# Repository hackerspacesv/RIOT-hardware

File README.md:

Hackerspace San Salvador RIOT OS Development Boards
===================================================
This repository contains all the design files for the boards supported by the
[RIOT OS](https://www.riot-os.org/) port mantained by the [Hackerspace
San Salvador](http://hackerspace.teubi.co/). You can find the RIOT OS port 
for the supported boards over
[https://github.com/hackerspacesv/RIOT](https://github.com/hackerspacesv/RIOT).

### Current boards supported
* **[ATSAMR21 Breakout Board](http://hackerspace.teubi.co/wiki/index.php?title=HSSV_ATSAMR21_Breakout_English)**: A development board to accelerate the deployment of
  IEEE 802.15.4 based networks on the 2.4Ghz band. It is based on the
  ATSAMR21G18-MR210UA module wich also includes support for antenna-diversity and
  a crypto-acceleration chip. This board was designed to be breadboard-friendly
  and includes USB support and power & LiPo battery management.
* **ATZB-RF-233-1-C breakout**: This is a breadboard-friendly breakout board for the
  module ATZB-RF-233-1-C, this module includes the easy-to-use AT8RF233 radio with
  a front-end-module with a Power-Amplifier & Low-Noise-Amplifier (PA/LNA) to greatly
  extend the range of the radio of IEEE 802.15.4 networks on the 2.4GHz band.

### Planned support
* **ATZB-RF-233-1-C breakout for the Omega Onion**: The Omega Onion is a low-cost
  system-on-a-module that runs a lightweight version of GNU/Linux. This breakout board
  should facilitate the creation of low-cost WiFi-802.15.4 bridges and edge routers.

### Board documentation

A guide to use this board with RIOT OS is available at the [Hackerspace San Salvador Wiki](http://hackerspace.teubi.co/wiki/index.php?title=HSSV_ATSAMR21_Breakout_English)

### Licensing and use
**Copyright 2018 Mario Gomez <mario.gomez@teubi.co>**

All files within this repository are licensed under the
Apache License, Version 2.0 (the "License") unless otherwise
specified in the individual files; you may not use this files
except in compliance with the License.

You may obtain a copy of the License at

    http://www.apache.org/licenses/LICENSE-2.0

Unless required by applicable law or agreed to in writing, software
and design files distributed under the License are distributed on an
"AS IS" BASIS, WITHOUT WARRANTIES OR CONDITIONS OF ANY KIND, either
express or implied.

See the License for the specific language governing permissions and
limitations under the License.

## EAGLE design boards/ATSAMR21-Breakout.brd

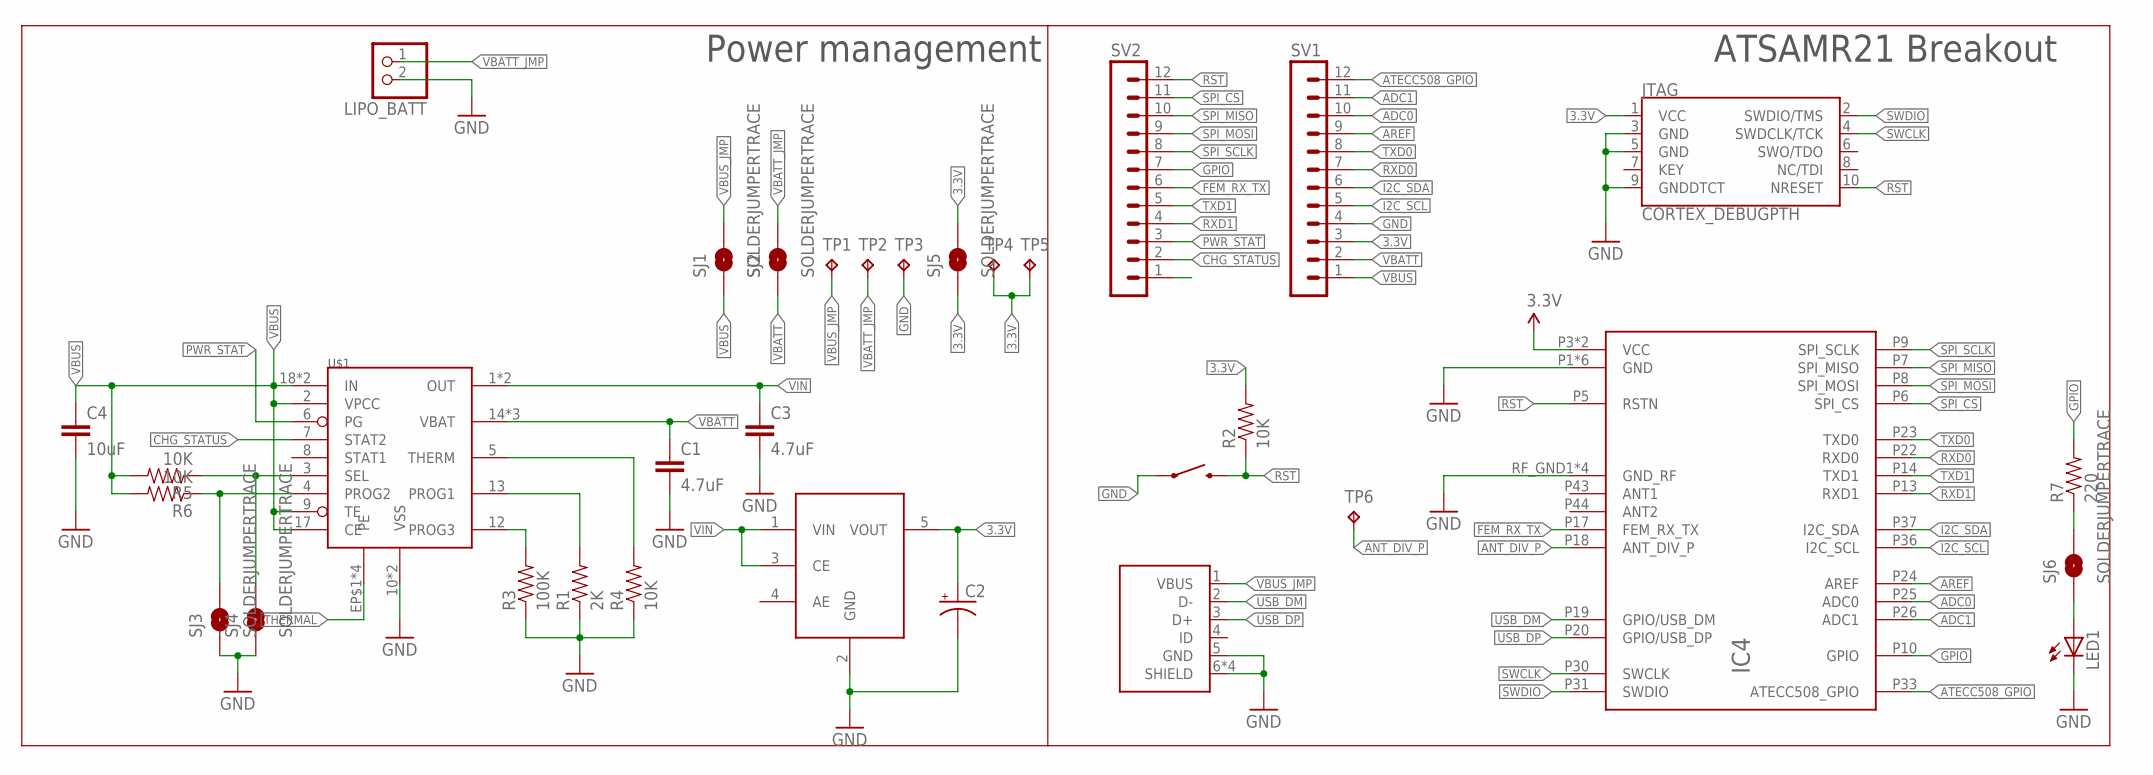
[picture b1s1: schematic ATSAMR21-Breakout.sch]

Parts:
C1, C3: 4.7uF; 0805
C2: 47uF; 1210-POLARIZED
C4: 10uF; 0805
IC3: NCP4589DSN33T1G; SOT23-5
IC4: ATSAMR21G18-MR210UA; ATSAMR21G18A-MR210UA
JTAG: CORTEX_DEBUGPTH; 2X5-PTH-1.27MM
LED1: LEDCHIPLED_1206; CHIPLED_1206
LIPO_BATT: JST_2PIN-THM-RA; JST-PH-2-THM-RA
R1: 2K; 0805
R2, R4, R5, R6: 10K; 0805
R3: 100K; 0805
R7: 220; 0805
S1: EVQ-PNF04M; PANASONIC_EVQPE1/PN/5P
SJ1, SJ2, SJ3, SJ4, SJ5, SJ6: SOLDERJUMPERTRACE; SJ_2S-TRACE
SV1, SV2: MA12-1
TP1, TP2, TP3, TP4, TP5, TP6: TPTP15R; TP15R
U$1: MCP73871T; QFN-20
USB_CONN: USB-MICRO-B; HPL511

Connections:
3.3V: C2.1 (+), IC3.5 (VOUT), IC4.P3 (VCC), IC4.P4 (VCC), JTAG.1 (VCC), R2.2, SJ5.1, SJ5.2, SV1.3, TP4.TP, TP5.TP
ADC0: IC4.P25 (ADC0), SV1.10
ADC1: IC4.P26 (ADC1), SV1.11
ANT_DIV_P: IC4.P18 (ANT_DIV_P), TP6.TP
AREF: IC4.P24 (AREF), SV1.9
ATECC508_GPIO: IC4.P33 (ATECC508_GPIO), SV1.12
CHG_STATUS: SV2.2, U$1.7 (STAT2)
FEM_RX_TX: IC4.P17 (FEM_RX_TX), SV2.6
GND: C1.2, C2.2 (-), C3.2, C4.2, IC3.2 (GND), IC4.P1 (GND), IC4.P2 (GND), IC4.P12 (GND), IC4.P29 (GND), IC4.P41 (GND), IC4.P42 (GND), IC4.RF_GND1 (GND_RF), IC4.RF_GND2 (GND_RF), IC4.RF_GND3 (GND_RF), IC4.RF_GND4 (GND_RF), JTAG.3 (GND), JTAG.5 (GND), JTAG.9 (GNDDTCT), LED1.C, LIPO_BATT.2 (1), R1.1, R3.1, R4.1, S1.P1 (1), SJ3.1, SJ4.1, SV1.4, SV2.1, TP3.TP, U$1.10 (VSS), U$1.11 (VSS), USB_CONN.5 (GND), USB_CONN.6 (SHIELD), USB_CONN.7 (SHIELD), USB_CONN.8 (SHIELD), USB_CONN.9 (SHIELD)
GPIO: IC4.P10 (GPIO), R7.2, SV2.7
I2C_SCL: IC4.P36 (I2C_SCL), SV1.5
I2C_SDA: IC4.P37 (I2C_SDA), SV1.6
unnamed: R6.1, SJ3.2, U$1.4 (PROG2)
unnamed: R5.1, SJ4.2, U$1.3 (SEL)
unnamed: R3.2, U$1.12 (PROG3)
unnamed: R1.2, U$1.13 (PROG1)
unnamed: R4.2, U$1.5 (THERM)
unnamed: LED1.A, SJ6.1
unnamed: R7.1, SJ6.2
PWR_STAT: SV2.3, U$1.6 (PG)
RST: IC4.P5 (RSTN), JTAG.10 (NRESET), R2.1, S1.P2 (2), SV2.12
RXD0: IC4.P22 (RXD0), SV1.7
RXD1: IC4.P13 (RXD1), SV2.4
SPI_CS: IC4.P6 (SPI_CS), SV2.11
SPI_MISO: IC4.P7 (SPI_MISO), SV2.10
SPI_MOSI: IC4.P8 (SPI_MOSI), SV2.9
SPI_SCLK: IC4.P9 (SPI_SCLK), SV2.8
SWCLK: IC4.P30 (SWCLK), JTAG.4 (SWDCLK/TCK)
SWDIO: IC4.P31 (SWDIO), JTAG.2 (SWDIO/TMS)
THERMAL: U$1.EP$1 (PE), U$1.EP$2 (PE), U$1.EP$3 (PE), U$1.EP$4 (PE)
TXD0: IC4.P23 (TXD0), SV1.8
TXD1: IC4.P14 (TXD1), SV2.5
USB_DM: IC4.P19 (GPIO/USB_DM), USB_CONN.2 (D-)
USB_DP: IC4.P20 (GPIO/USB_DP), USB_CONN.3 (D+)
VBATT: C1.1, SJ2.1, SV1.2, U$1.14 (VBAT), U$1.15 (VBAT), U$1.16 (VBAT)
VBATT_JMP: LIPO_BATT.1 (2), SJ2.2, TP2.TP
VBUS: C4.1, R5.2, R6.2, SJ1.1, SV1.1, U$1.2 (VPCC), U$1.9 (TE), U$1.17 (CE), U$1.18 (IN), U$1.19 (IN)
VBUS_JMP: SJ1.2, TP1.TP, USB_CONN.1 (VBUS)
VIN: C3.1, IC3.1 (VIN), IC3.3 (CE), U$1.1 (OUT), U$1.20 (OUT)

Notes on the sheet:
Power management
ATSAMR21 Breakout

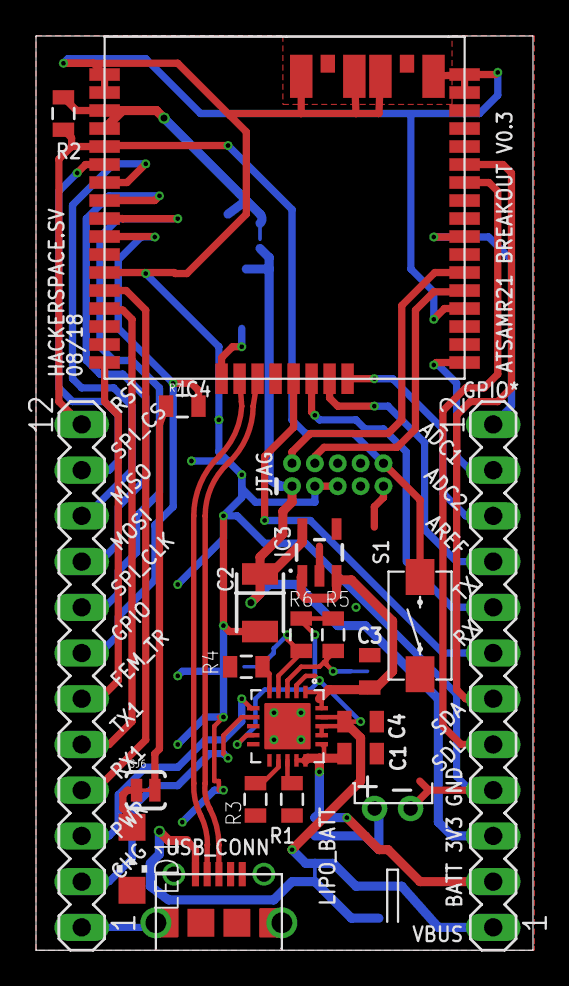
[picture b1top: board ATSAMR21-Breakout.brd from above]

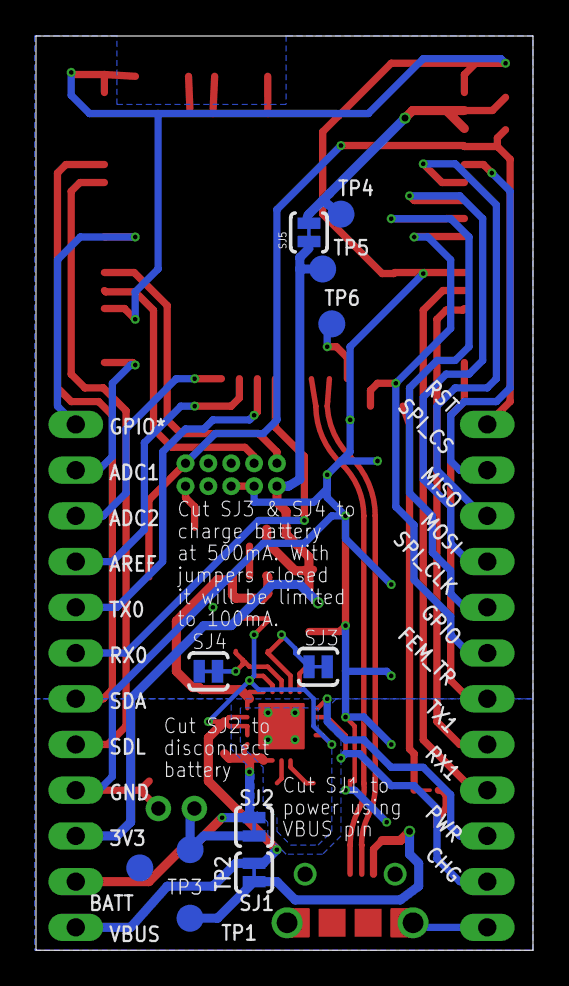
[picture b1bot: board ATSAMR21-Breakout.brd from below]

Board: 2 copper layers, 27.6 x 50.8 mm, 33 parts (11 on the bottom side), 39 nets.

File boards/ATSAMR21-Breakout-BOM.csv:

"Qty";"Value";"Device";"Package";"Parts";"Description";"MF";"MPN";"OC_FARNELL";"OC_NEWARK";"PROD_ID";"TP_SIGNAL_NAME";"VALUE";
"1";"";"JST_2PIN-THM-RA";"JST-PH-2-THM-RA";"LIPO_BATT";"JST 2-Pin Connectors of various flavors";"";"";"";"";"";"";"";
"2";"";"MA12-1";"MA12-1";"SV1, SV2";"PIN HEADER";"";"";"unknown";"unknown";"";"";"";
"1";"100K";"RESISTOR0805-RES";"0805";"R3";"Resistor";"";"";"";"";"";"";"";
"4";"10K";"RESISTOR0805-RES";"0805";"R2, R4, R5, R6";"Resistor";"";"";"";"";"";"";"";
"1";"10uF";"22UF-0805-6.3V-20%";"0805";"C4";"22µF ceramic capacitors";"";"";"";"";"CAP-08402";"";"22uF";
"1";"2K";"RESISTOR0805-RES";"0805";"R1";"Resistor";"";"";"";"";"";"";"";
"2";"4.7uF";"22UF-0805-6.3V-20%";"0805";"C1, C3";"22µF ceramic capacitors";"";"";"";"";"CAP-08402";"";"22uF";
"1";"47uF";"TPSB107M010R0400";"1210-POLARIZED";"C2";"";"";"";"";"";"";"";"";
"1";"ATSAMR21G18-MR210UA";"ATSAMR21G18-MR210UA";"ATSAMR21G18A-MR210UA";"IC4";"";"";"";"";"";"";"";"";
"1";"CORTEX_DEBUGPTH";"CORTEX_DEBUGPTH";"2X5-PTH-1.27MM";"JTAG";"Cortex Debug Connector";"";"";"";"";"";"";"";
"1";"EVQ-PNF04M";"EVQ-PNF04M";"PANASONIC_EVQPE1/PN/5P";"S1";"";"";"";"";"";"";"";"";
"1";"MCP73871T";"MCP73871T";"QFN-20";"U$1";"";"";"";"";"";"";"";"";
"1";"NCP4589DSN33T1G";"NCP4589DSN33T1G";"SOT23-5";"IC3";"";"";"";"";"";"";"";"";
"4";"SOLDERJUMPERTRACE";"SOLDERJUMPERTRACE";"SJ_2S-TRACE";"SJ1, SJ2, SJ3, SJ4";"Solder Jumper";"";"";"";"";"";"";"";
"3";"TPB2,54";"TPB2,54";"B2,54";"TP1, TP2, TP3";"Test pad";"";"";"";"";"";"";"";
"1";"USB-MICRO-B";"USB-MICRO-B";"HPL511";"USB_CONN";"";"";"";"";"";"";"";"";

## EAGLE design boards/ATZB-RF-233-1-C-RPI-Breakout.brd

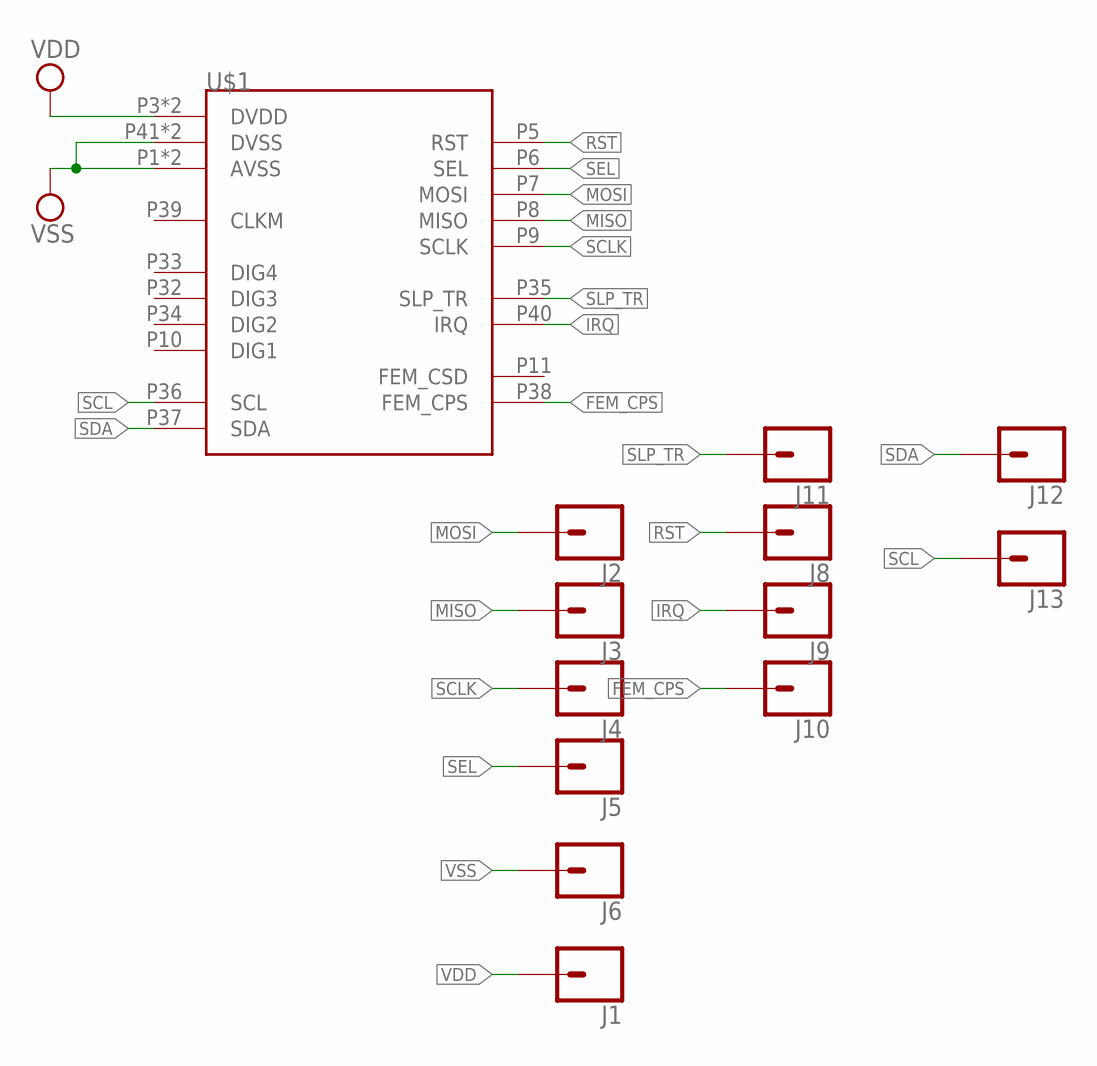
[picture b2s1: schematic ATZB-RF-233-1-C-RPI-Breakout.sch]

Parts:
J1, J2, J3, J4, J5, J6, J8, J9, J10, J11, J12, J13: CONN_01OFFSET; 1X01_OFFSET
U$1: ATZB-RF-233-1-C

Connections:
FEM_CPS: J10.1, U$1.P38 (FEM_CPS)
IRQ: J9.1, U$1.P40 (IRQ)
MISO: J3.1, U$1.P8 (MISO)
MOSI: J2.1, U$1.P7 (MOSI)
RST: J8.1, U$1.P5 (RST)
SCL: J13.1, U$1.P36 (SCL)
SCLK: J4.1, U$1.P9 (SCLK)
SDA: J12.1, U$1.P37 (SDA)
SEL: J5.1, U$1.P6 (SEL)
SLP_TR: J11.1, U$1.P35 (SLP_TR)
VDD: J1.1, U$1.P3 (DVDD), U$1.P4 (DVDD)
VSS: J6.1, U$1.P1 (AVSS), U$1.P2 (AVSS), U$1.P41 (DVSS), U$1.P42 (DVSS)

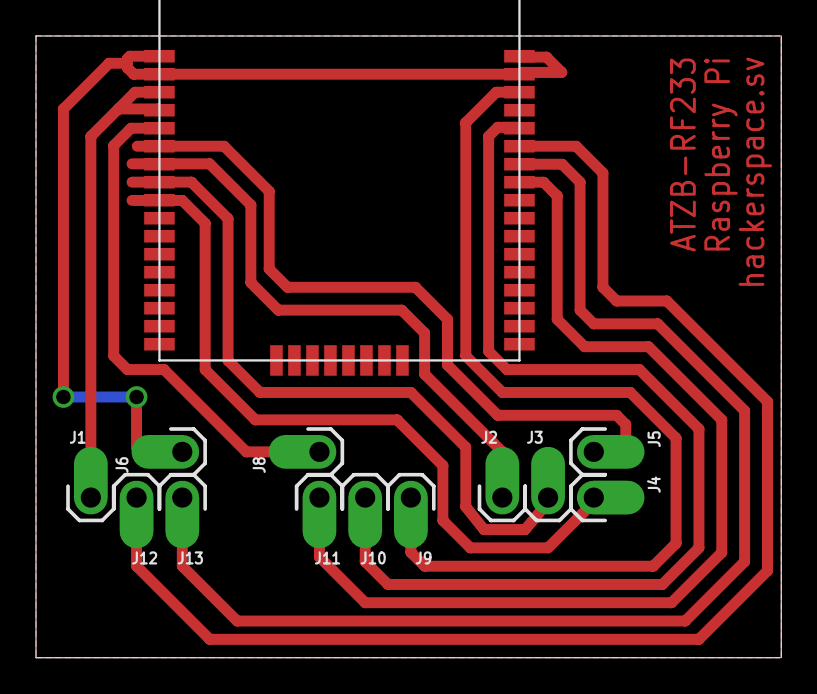
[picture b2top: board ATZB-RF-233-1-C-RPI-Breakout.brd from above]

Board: 2 copper layers, 41.4 x 34.5 mm, 13 parts (0 on the bottom side), 12 nets.

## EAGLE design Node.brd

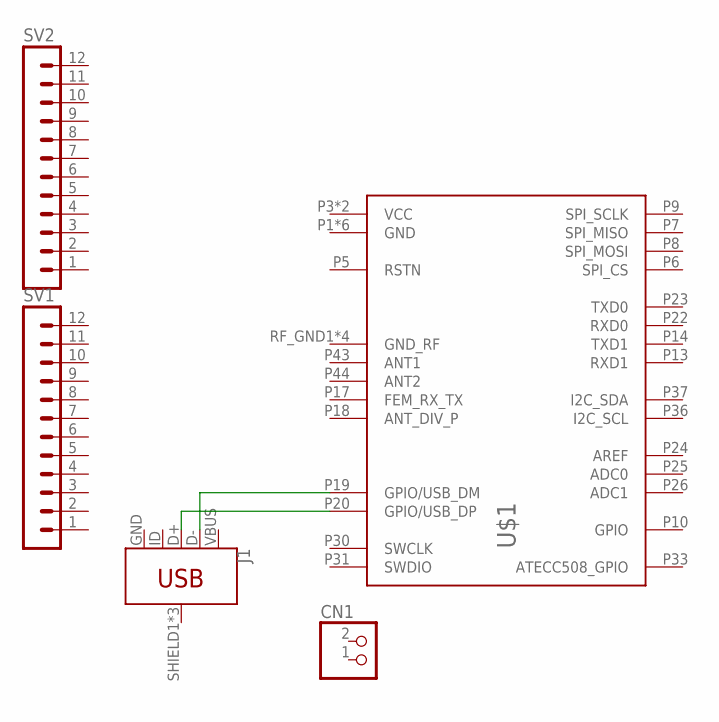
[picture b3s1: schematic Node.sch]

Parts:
CN1: JST_2PIN-THM-RA; JST-PH-2-THM-RA
J1: USB_MICRO-B_FEMALE-SMT; USB-B-MICRO-SMD
SV1, SV2: MA12-1
U$1: ATSAMR21G18-MR210UA; ATSAMR21G18A-MR210UA

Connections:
AREF: U$1.P24 (AREF)
GND: J1.GND, U$1.P1 (GND), U$1.P2 (GND), U$1.P12 (GND), U$1.P29 (GND), U$1.P41 (GND), U$1.P42 (GND)
unnamed: J1.D-, U$1.P19 (GPIO/USB_DM)
unnamed: J1.D+, U$1.P20 (GPIO/USB_DP)
VBUS: J1.VBUS
VCC: U$1.P3 (VCC), U$1.P4 (VCC)

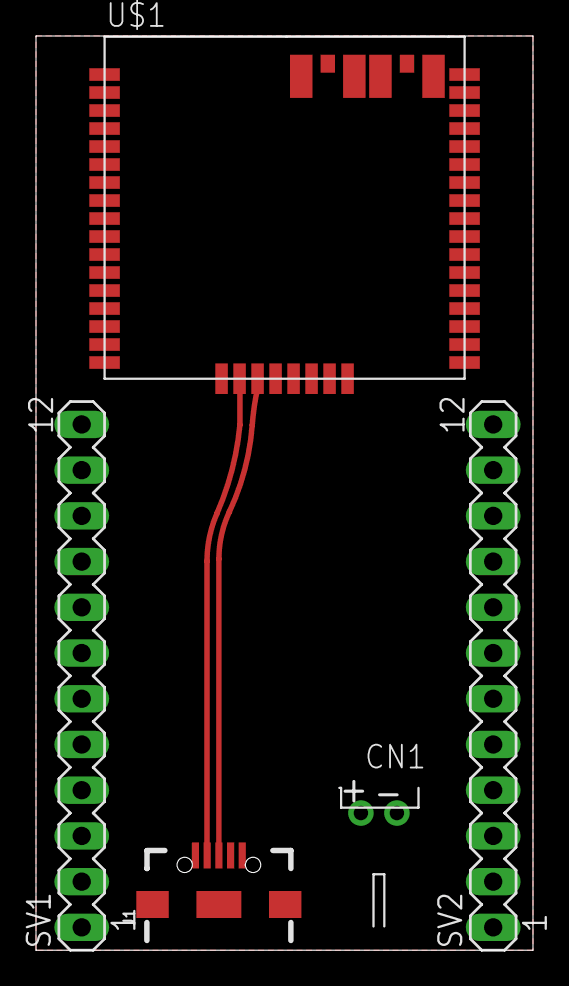
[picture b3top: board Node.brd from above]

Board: 2 copper layers, 27.6 x 50.8 mm, 5 parts (0 on the bottom side), 4 nets.

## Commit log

2018-03-30 Added land pattern for ATSAMR21G18-MR210UA and ATZB-RF-233-1-CR
2018-03-31 Finished breakout board for ATSAMR21 This version is available at OSHPark Changes: +Breakout board finished +BOM updated with available components +Fixed directory structure
2018-04-01 Added breakout board for ATZB-RF-233-1-C.
2018-04-01 Added Apache 2.0 License
    Added licensing info
2018-04-01 Added README.md
    Added README.md
2018-04-03 Added Arduino examples for Teensy and ATZB-RF-233-1-C
2018-06-10 Added PDF versions of schematic files.
2018-06-16 Added new breakout board for ATZB-RF233 for Raspberry Pi.
2018-08-06 Changed Power-Path design.
2018-08-06 Fixed charge management symbol
2018-09-23 Added an script for programming the bootloader onto the atsamr21-breakout board.
2018-09-23 Fixed makefile with newest bootloader.
2018-09-23 Minor fixes to the bootloader flasher makefile for the atsamr21-breakout board.
2018-09-24 Added link to Hackerspace Wiki
2018-09-30 Update info about RIOT.
2018-10-16 Added LED and re-routed chg-mgmt signals.

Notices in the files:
parts and their libraries:
SparkFun-Connectors: Licensing: Creative Commons ShareAlike 4.0 International - https://creativecommons.org/licenses/by-sa/4.0
